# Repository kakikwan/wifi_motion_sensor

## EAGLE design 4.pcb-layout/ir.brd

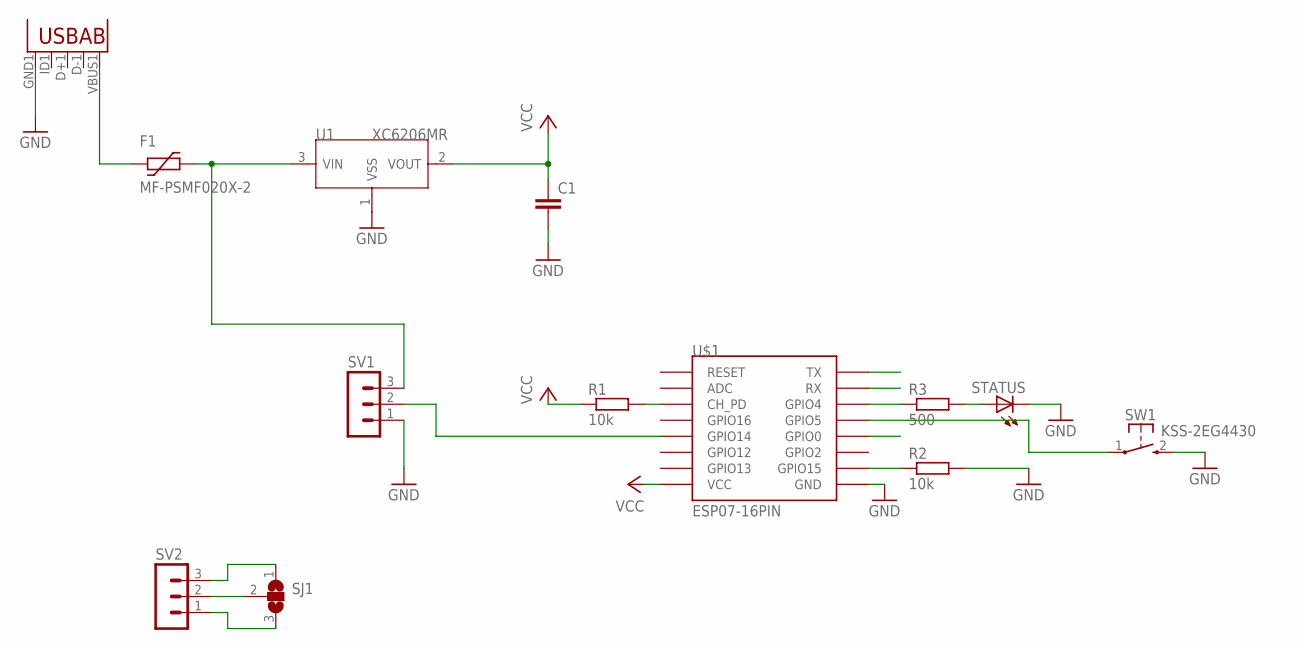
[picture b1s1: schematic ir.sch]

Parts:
C1: C-EUC0805; C0805
F1: MF-PSMF020X-2; 0805L
R1, R2: 10k; R0805
R3: 500; R0805
SJ1: SJ2W; SJ_2
STATUS: LEDCHIPLED_0805; CHIPLED_0805
SV1, SV2: MA03-1
SW1: KSS-2EG4430
U1: XC6206MR; SOT23
U2: USB""; USB-MICRO-SMD
U$1: ESP07-16PIN

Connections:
FLASH: U$1.GPIO0
GND: C1.2, R2.2, STATUS.C, SV1.1, SW1.2 (S), U1.1 (VSS), U2.GND1 (GND), U$1.GND
unnamed: R1.2, U$1.CH_PD
unnamed: R2.1, U$1.GPIO15
unnamed: F1.2, SV1.3, U1.3 (VIN)
unnamed: SW1.1, U$1.GPIO5
unnamed: F1.1, U2.VBUS1 (VBUS)
unnamed: SV1.2, U$1.GPIO14
unnamed: R3.1, U$1.GPIO4
unnamed: R3.2, STATUS.A
unnamed: SJ1.2, SV2.2
unnamed: SJ1.1, SV2.3
unnamed: SJ1.3, SV2.1
RX: U$1.RX
TX: U$1.TX
VCC: C1.1, R1.1, U1.2 (VOUT), U$1.VCC

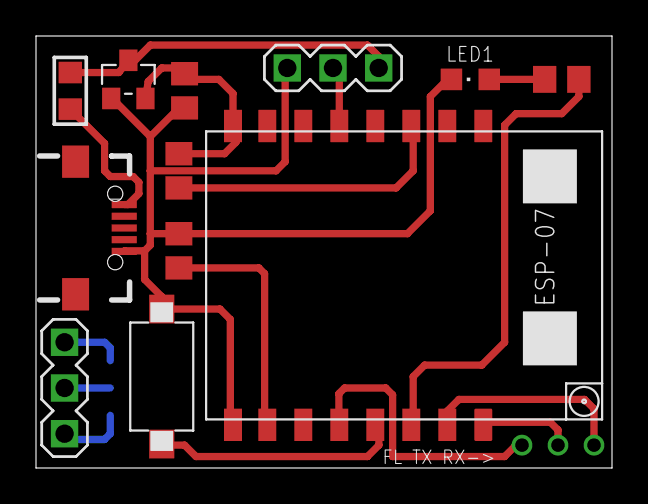
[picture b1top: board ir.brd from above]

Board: 2 copper layers, 32.0 x 24.0 mm, 13 parts (1 on the bottom side), 13 nets.

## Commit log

2016-12-03 Create temp
